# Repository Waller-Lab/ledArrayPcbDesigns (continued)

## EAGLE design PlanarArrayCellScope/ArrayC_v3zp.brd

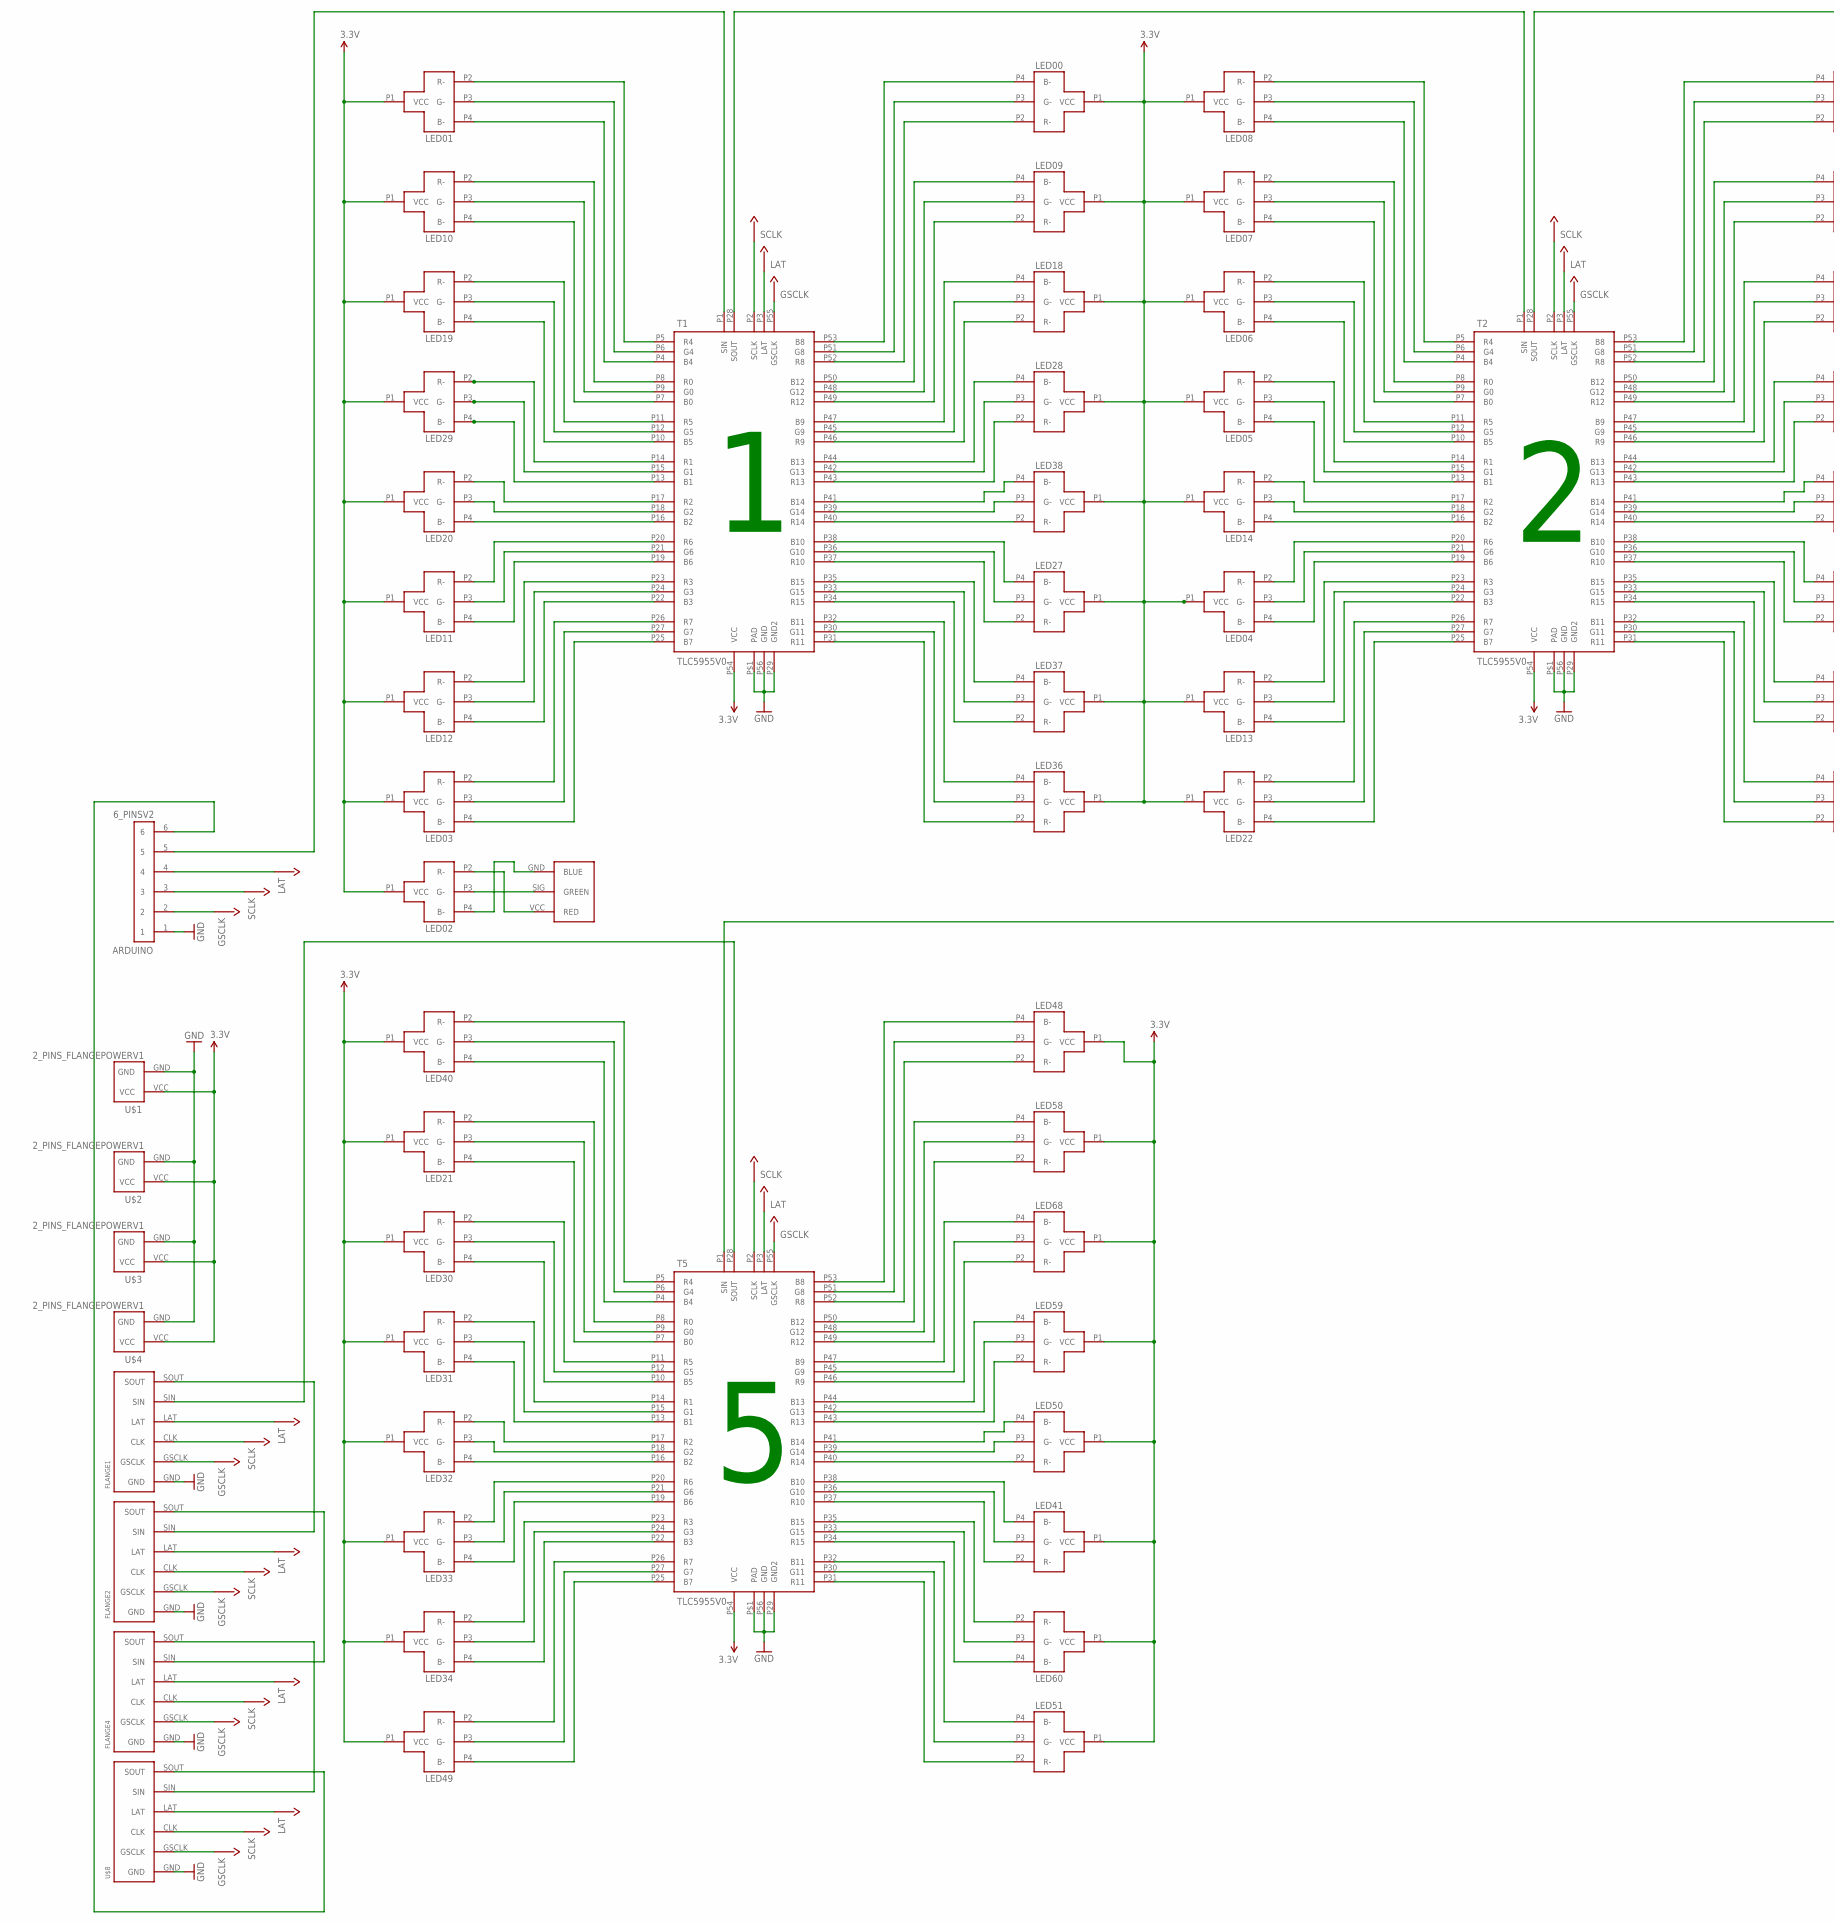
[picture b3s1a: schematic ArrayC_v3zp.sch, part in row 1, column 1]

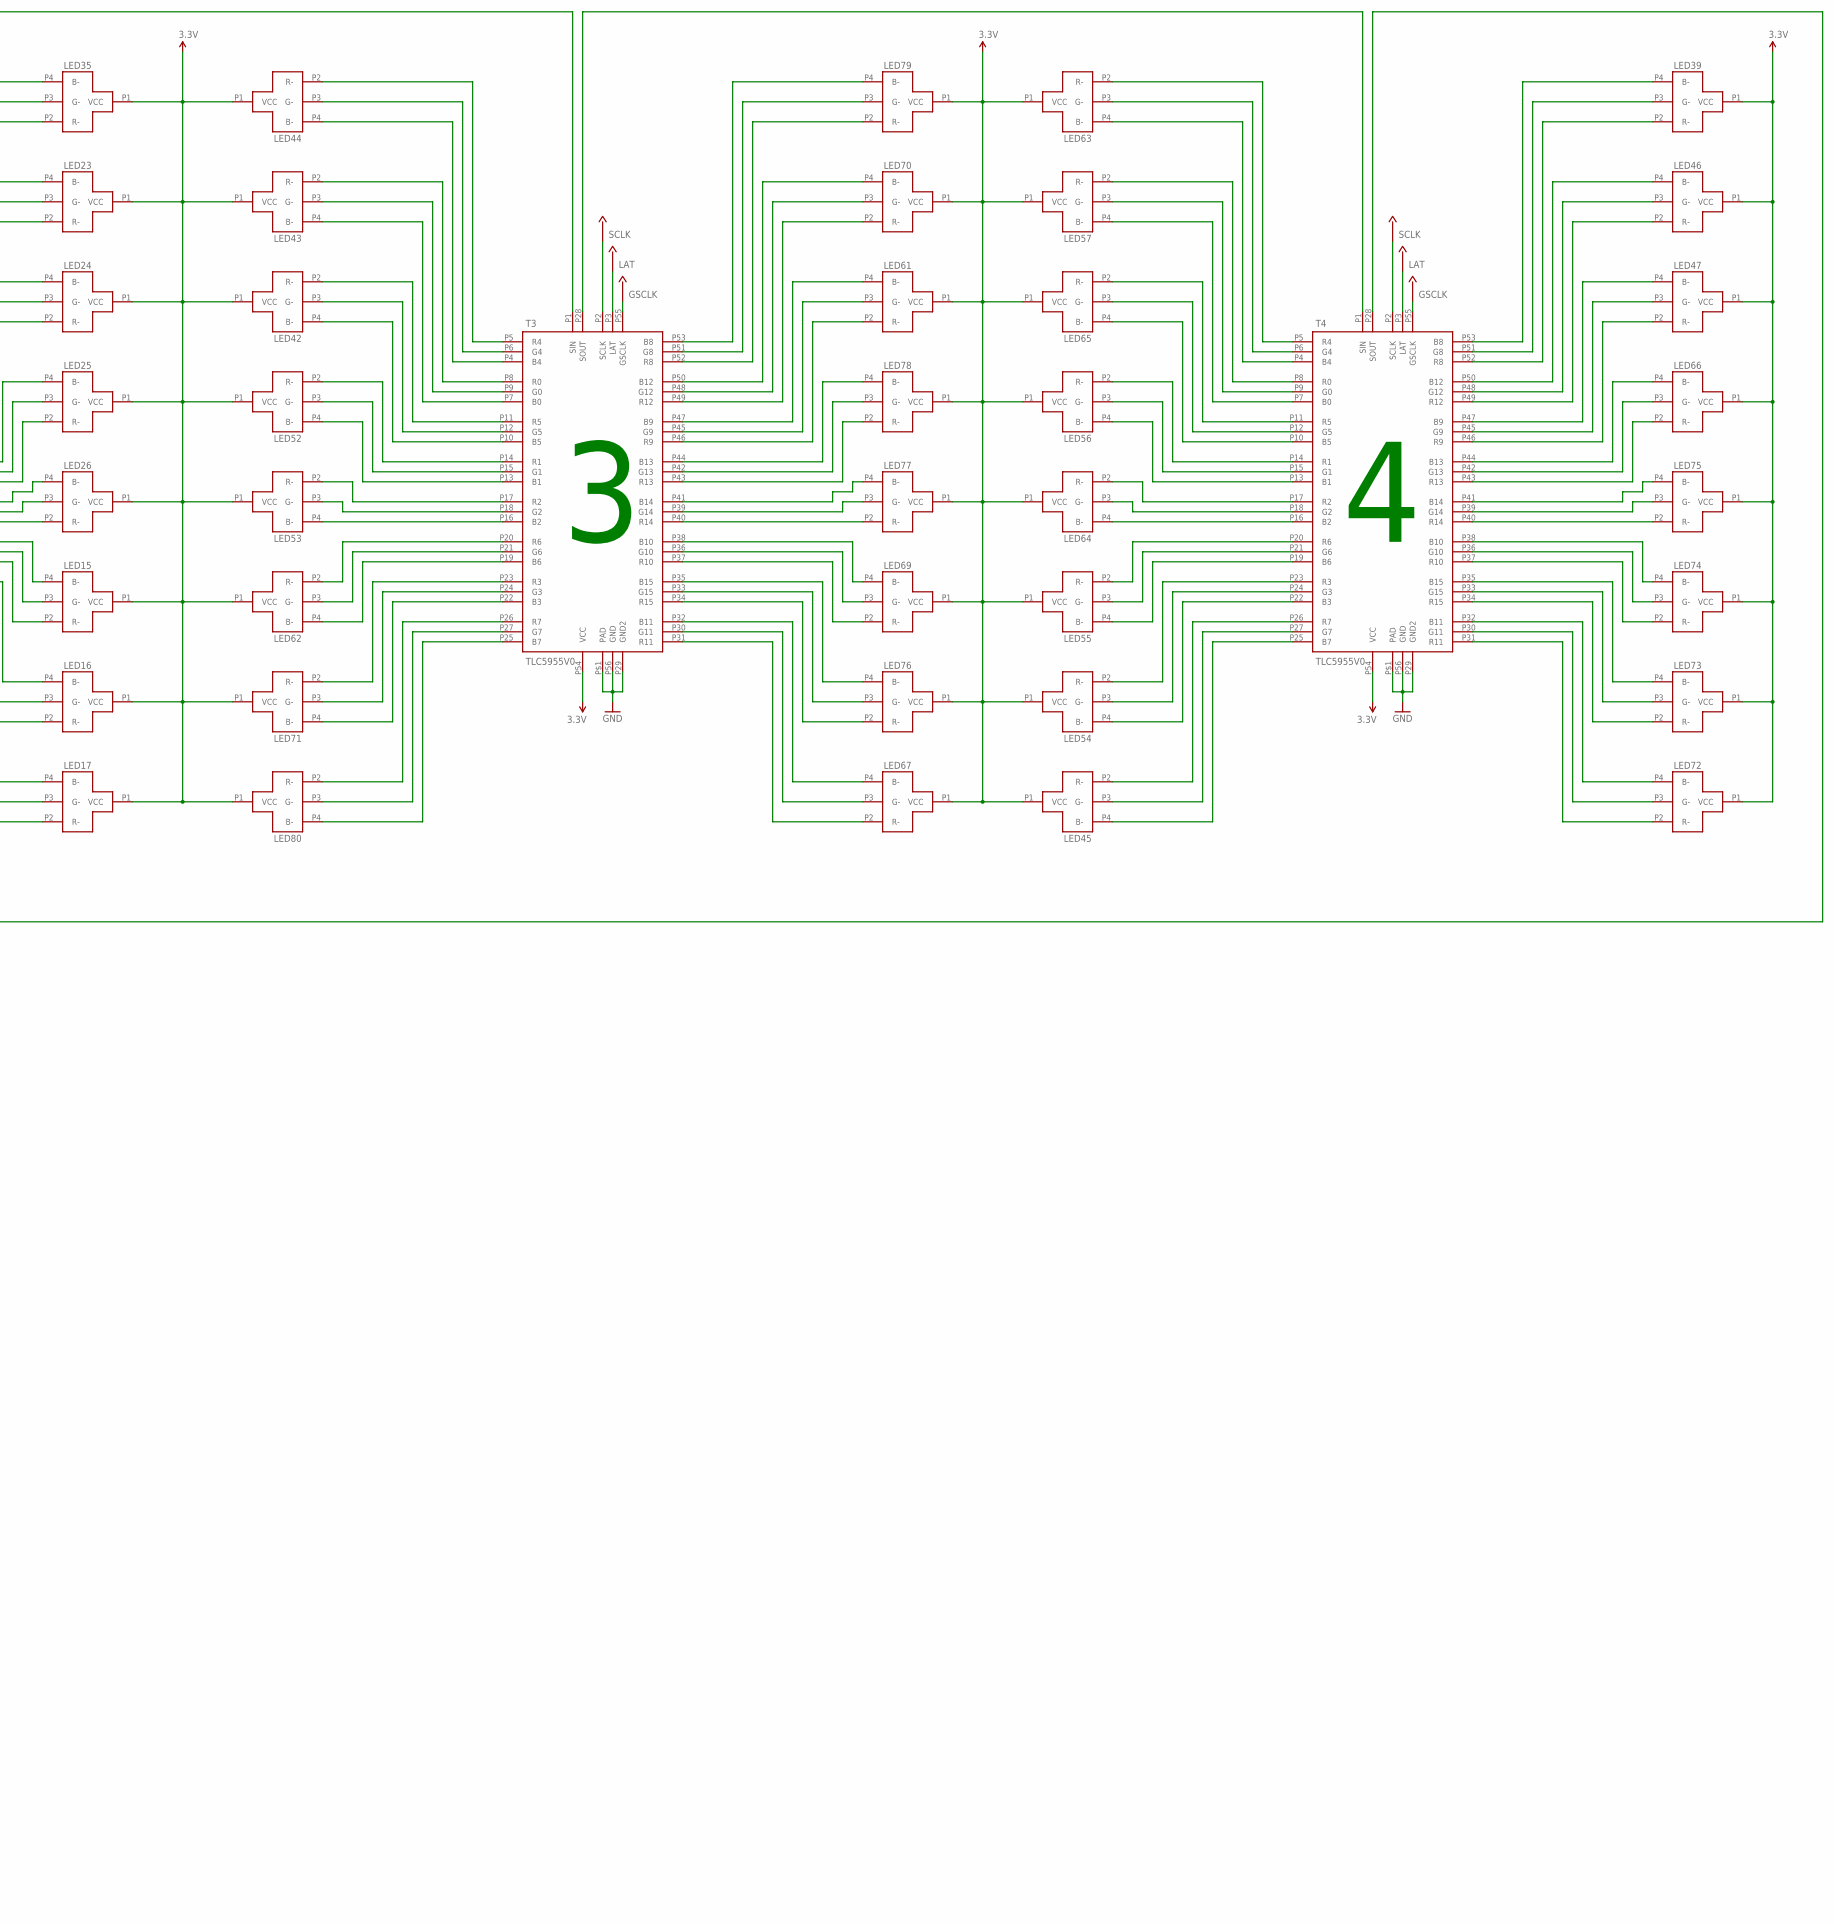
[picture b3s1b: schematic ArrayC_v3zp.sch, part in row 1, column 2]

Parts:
ARDUINO: 6_PINSV2; 6PIN_SMD
FLANGE1, FLANGE2, FLANGE4: 6PINS_LEDFLANGEV1; 6PIN_PADS
LED: 3_PINS_RGBV1; 3PIN_HOLES
LED00, LED01, LED02, LED03, LED04, LED05, LED06, LED07, LED08, LED09, LED10, LED11, LED12, LED13, LED14, LED15, LED16, LED17, LED18, LED19, LED20, LED21, LED22, LED23, LED24, LED25, LED26, LED27, LED28, LED29, LED30, LED31, LED32, LED33, LED34, LED35, LED36, LED37, LED38, LED39, LED40, LED41, LED42, LED43, LED44, LED45, LED46, LED47, LED48, LED49, LED50, LED51, LED52, LED53, LED54, LED55, LED56, LED57, LED58, LED59, LED60, LED61, LED62, LED63, LED64, LED65, LED66, LED67, LED68, LED69, LED70, LED71, LED72, LED73, LED74, LED75, LED76, LED77, LED78, LED79, LED80: KB_APTF1616V0; KB_RGBLED_APTF1616
T1, T2, T3, T4, T5: TLC5955V0; 56-HTSSOP
U$1, U$2, U$3, U$4: 2_PINS_FLANGEPOWERV1; 2PIN_PADS_PWR
U$8: 6PINS_LEDFLANGEV1; 6PIN_PADS

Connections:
3.3V: LED01.P1 (VCC), LED02.P1 (VCC), LED03.P1 (VCC), LED10.P1 (VCC), LED11.P1 (VCC), LED12.P1 (VCC), LED19.P1 (VCC), LED20.P1 (VCC), LED21.P1 (VCC), LED29.P1 (VCC), LED30.P1 (VCC), LED31.P1 (VCC), LED32.P1 (VCC), LED33.P1 (VCC), LED34.P1 (VCC), LED39.P1 (VCC), LED40.P1 (VCC), LED41.P1 (VCC), LED45.P1 (VCC), LED46.P1 (VCC), LED47.P1 (VCC), LED48.P1 (VCC), LED49.P1 (VCC), LED50.P1 (VCC), LED51.P1 (VCC), LED54.P1 (VCC), LED55.P1 (VCC), LED56.P1 (VCC), LED57.P1 (VCC), LED58.P1 (VCC), LED59.P1 (VCC), LED60.P1 (VCC), LED61.P1 (VCC), LED63.P1 (VCC), LED64.P1 (VCC), LED65.P1 (VCC), LED66.P1 (VCC), LED67.P1 (VCC), LED68.P1 (VCC), LED69.P1 (VCC), LED70.P1 (VCC), LED72.P1 (VCC), LED73.P1 (VCC), LED74.P1 (VCC), LED75.P1 (VCC), LED76.P1 (VCC), LED77.P1 (VCC), LED78.P1 (VCC), LED79.P1 (VCC), T1.P54 (VCC), T2.P54 (VCC), T3.P54 (VCC), T4.P54 (VCC), T5.P54 (VCC), U$1.VCC, U$2.VCC, U$3.VCC, U$4.VCC
GND: ARDUINO.1, FLANGE1.GND, FLANGE2.GND, FLANGE4.GND, T1.P29 (GND2), T1.P56 (GND), T1.P$1 (PAD), T2.P29 (GND2), T2.P56 (GND), T2.P$1 (PAD), T3.P29 (GND2), T3.P56 (GND), T3.P$1 (PAD), T4.P29 (GND2), T4.P56 (GND), T4.P$1 (PAD), T5.P29 (GND2), T5.P56 (GND), T5.P$1 (PAD), U$1.GND, U$2.GND, U$3.GND, U$4.GND, U$8.GND
GSCLK: ARDUINO.2, FLANGE1.GSCLK, FLANGE2.GSCLK, FLANGE4.GSCLK, T1.P55 (GSCLK), T2.P55 (GSCLK), T3.P55 (GSCLK), T4.P55 (GSCLK), T5.P55 (GSCLK), U$8.GSCLK
LAT: ARDUINO.4, FLANGE1.LAT, FLANGE2.LAT, FLANGE4.LAT, T1.P3 (LAT), T2.P3 (LAT), T3.P3 (LAT), T4.P3 (LAT), T5.P3 (LAT), U$8.LAT
unnamed: LED40.P2 (R-), T5.P5 (R4)
unnamed: LED40.P3 (G-), T5.P6 (G4)
unnamed: LED40.P4 (B-), T5.P4 (B4)
unnamed: LED21.P2 (R-), T5.P8 (R0)
unnamed: LED21.P3 (G-), T5.P9 (G0)
unnamed: LED21.P4 (B-), T5.P7 (B0)
unnamed: LED30.P2 (R-), T5.P11 (R5)
unnamed: LED30.P3 (G-), T5.P12 (G5)
unnamed: LED30.P4 (B-), T5.P10 (B5)
unnamed: LED31.P2 (R-), T5.P14 (R1)
unnamed: LED31.P3 (G-), T5.P15 (G1)
unnamed: LED31.P4 (B-), T5.P13 (B1)
unnamed: LED32.P2 (R-), T5.P17 (R2)
unnamed: LED32.P3 (G-), T5.P18 (G2)
unnamed: LED32.P4 (B-), T5.P16 (B2)
unnamed: LED33.P2 (R-), T5.P20 (R6)
unnamed: LED33.P3 (G-), T5.P21 (G6)
unnamed: LED33.P4 (B-), T5.P19 (B6)
unnamed: LED34.P2 (R-), T5.P23 (R3)
unnamed: LED34.P3 (G-), T5.P24 (G3)
unnamed: LED34.P4 (B-), T5.P22 (B3)
unnamed: LED49.P2 (R-), T5.P26 (R7)
unnamed: LED49.P3 (G-), T5.P27 (G7)
unnamed: LED49.P4 (B-), T5.P25 (B7)
unnamed: LED48.P4 (B-), T5.P53 (B8)
unnamed: LED48.P3 (G-), T5.P51 (G8)
unnamed: LED48.P2 (R-), T5.P52 (R8)
unnamed: LED58.P4 (B-), T5.P50 (B12)
unnamed: LED58.P3 (G-), T5.P48 (G12)
unnamed: LED58.P2 (R-), T5.P49 (R12)
unnamed: LED68.P4 (B-), T5.P47 (B9)
unnamed: LED68.P3 (G-), T5.P45 (G9)
unnamed: LED68.P2 (R-), T5.P46 (R9)
unnamed: LED59.P4 (B-), T5.P44 (B13)
unnamed: LED59.P3 (G-), T5.P42 (G13)
unnamed: LED50.P4 (B-), T5.P41 (B14)
unnamed: LED50.P3 (G-), T5.P39 (G14)
unnamed: LED50.P2 (R-), T5.P40 (R14)
unnamed: LED41.P4 (B-), T5.P38 (B10)
unnamed: LED41.P3 (G-), T5.P36 (G10)
unnamed: LED41.P2 (R-), T5.P37 (R10)
unnamed: LED60.P2 (R-), T5.P35 (B15)
unnamed: LED60.P3 (G-), T5.P33 (G15)
unnamed: LED60.P4 (B-), T5.P34 (R15)
unnamed: LED51.P4 (B-), T5.P32 (B11)
unnamed: LED51.P3 (G-), T5.P30 (G11)
unnamed: LED51.P2 (R-), T5.P31 (R11)
unnamed: LED.VCC (RED), LED02.P2 (R-)
unnamed: LED.GND (BLUE), LED02.P4 (B-)
unnamed: LED.SIG (GREEN), LED02.P3 (G-)
unnamed: FLANGE1.SOUT, FLANGE2.SIN
unnamed: FLANGE2.SOUT, FLANGE4.SIN
unnamed: ARDUINO.6, U$8.SOUT
unnamed: FLANGE4.SOUT, U$8.SIN
unnamed: LED01.P2 (R-), T1.P5 (R4)
unnamed: LED01.P3 (G-), T1.P6 (G4)
unnamed: LED01.P4 (B-), T1.P4 (B4)
unnamed: LED10.P2 (R-), T1.P8 (R0)
unnamed: LED10.P3 (G-), T1.P9 (G0)
unnamed: LED10.P4 (B-), T1.P7 (B0)
unnamed: LED19.P2 (R-), T1.P11 (R5)
unnamed: LED19.P3 (G-), T1.P12 (G5)
unnamed: LED19.P4 (B-), T1.P10 (B5)
unnamed: LED29.P2 (R-), T1.P14 (R1)
unnamed: LED29.P3 (G-), T1.P15 (G1)
unnamed: LED29.P4 (B-), T1.P13 (B1)
unnamed: LED20.P2 (R-), T1.P17 (R2)
unnamed: LED20.P3 (G-), T1.P18 (G2)
unnamed: LED20.P4 (B-), T1.P16 (B2)
unnamed: LED11.P2 (R-), T1.P20 (R6)
unnamed: LED11.P3 (G-), T1.P21 (G6)
unnamed: LED11.P4 (B-), T1.P19 (B6)
unnamed: LED12.P2 (R-), T1.P23 (R3)
unnamed: LED12.P3 (G-), T1.P24 (G3)
unnamed: LED12.P4 (B-), T1.P22 (B3)
unnamed: LED03.P2 (R-), T1.P26 (R7)
unnamed: LED03.P3 (G-), T1.P27 (G7)
unnamed: LED03.P4 (B-), T1.P25 (B7)
unnamed: LED00.P4 (B-), T1.P53 (B8)
unnamed: LED00.P3 (G-), T1.P51 (G8)
unnamed: LED00.P2 (R-), T1.P52 (R8)
unnamed: LED09.P4 (B-), T1.P50 (B12)
unnamed: LED09.P3 (G-), T1.P48 (G12)
unnamed: LED09.P2 (R-), T1.P49 (R12)
unnamed: LED18.P4 (B-), T1.P47 (B9)
unnamed: LED18.P3 (G-), T1.P45 (G9)
unnamed: LED18.P2 (R-), T1.P46 (R9)
unnamed: LED28.P4 (B-), T1.P44 (B13)
unnamed: LED28.P3 (G-), T1.P42 (G13)
unnamed: LED38.P4 (B-), T1.P41 (B14)
unnamed: LED38.P3 (G-), T1.P39 (G14)
unnamed: LED38.P2 (R-), T1.P40 (R14)
unnamed: LED27.P4 (B-), T1.P38 (B10)
unnamed: LED27.P3 (G-), T1.P36 (G10)
unnamed: LED27.P2 (R-), T1.P37 (R10)
unnamed: LED37.P4 (B-), T1.P35 (B15)
unnamed: LED37.P3 (G-), T1.P33 (G15)
unnamed: LED37.P2 (R-), T1.P34 (R15)
unnamed: LED36.P4 (B-), T1.P32 (B11)
unnamed: LED36.P3 (G-), T1.P30 (G11)
unnamed: LED36.P2 (R-), T1.P31 (R11)
unnamed: LED44.P2 (R-), T3.P5 (R4)
unnamed: LED08.P2 (R-), T2.P5 (R4)
unnamed: LED08.P3 (G-), T2.P6 (G4)
unnamed: LED08.P4 (B-), T2.P4 (B4)
unnamed: LED07.P2 (R-), T2.P8 (R0)
unnamed: LED07.P3 (G-), T2.P9 (G0)
unnamed: LED07.P4 (B-), T2.P7 (B0)
unnamed: LED06.P2 (R-), T2.P11 (R5)
unnamed: LED06.P3 (G-), T2.P12 (G5)
unnamed: LED06.P4 (B-), T2.P10 (B5)
unnamed: LED05.P2 (R-), T2.P14 (R1)
unnamed: LED05.P3 (G-), T2.P15 (G1)
unnamed: LED05.P4 (B-), T2.P13 (B1)
unnamed: LED14.P2 (R-), T2.P17 (R2)
unnamed: LED14.P3 (G-), T2.P18 (G2)
unnamed: LED14.P4 (B-), T2.P16 (B2)
unnamed: LED04.P2 (R-), T2.P20 (R6)
unnamed: LED04.P3 (G-), T2.P21 (G6)
unnamed: LED04.P4 (B-), T2.P19 (B6)
unnamed: LED13.P2 (R-), T2.P23 (R3)
unnamed: LED13.P3 (G-), T2.P24 (G3)
unnamed: LED13.P4 (B-), T2.P22 (B3)
unnamed: LED22.P2 (R-), T2.P26 (R7)
unnamed: LED22.P3 (G-), T2.P27 (G7)
unnamed: LED22.P4 (B-), T2.P25 (B7)
unnamed: LED35.P4 (B-), T2.P53 (B8)
unnamed: LED35.P3 (G-), T2.P51 (G8)
unnamed: LED35.P2 (R-), T2.P52 (R8)
unnamed: LED23.P4 (B-), T2.P50 (B12)
unnamed: LED23.P3 (G-), T2.P48 (G12)
unnamed: LED23.P2 (R-), T2.P49 (R12)
unnamed: LED24.P4 (B-), T2.P47 (B9)
unnamed: LED24.P3 (G-), T2.P45 (G9)
unnamed: LED24.P2 (R-), T2.P46 (R9)
unnamed: LED25.P4 (B-), T2.P44 (B13)
unnamed: LED25.P3 (G-), T2.P42 (G13)
unnamed: LED26.P4 (B-), T2.P41 (B14)
unnamed: LED26.P3 (G-), T2.P39 (G14)
unnamed: LED26.P2 (R-), T2.P40 (R14)
unnamed: LED15.P4 (B-), T2.P38 (B10)
unnamed: LED15.P3 (G-), T2.P36 (G10)
unnamed: LED15.P2 (R-), T2.P37 (R10)
unnamed: LED16.P4 (B-), T2.P35 (B15)
unnamed: LED16.P3 (G-), T2.P33 (G15)
unnamed: LED16.P2 (R-), T2.P34 (R15)
unnamed: LED17.P4 (B-), T2.P32 (B11)
unnamed: LED17.P3 (G-), T2.P30 (G11)
unnamed: LED17.P2 (R-), T2.P31 (R11)
unnamed: LED44.P3 (G-), T3.P6 (G4)
unnamed: LED44.P4 (B-), T3.P4 (B4)
unnamed: LED43.P2 (R-), T3.P8 (R0)
unnamed: LED43.P3 (G-), T3.P9 (G0)
unnamed: LED43.P4 (B-), T3.P7 (B0)
unnamed: LED42.P2 (R-), T3.P11 (R5)
unnamed: LED42.P3 (G-), T3.P12 (G5)
unnamed: LED42.P4 (B-), T3.P10 (B5)
unnamed: LED52.P2 (R-), T3.P14 (R1)
unnamed: LED52.P3 (G-), T3.P15 (G1)
unnamed: LED52.P4 (B-), T3.P13 (B1)
unnamed: LED53.P2 (R-), T3.P17 (R2)
unnamed: LED53.P3 (G-), T3.P18 (G2)
unnamed: LED53.P4 (B-), T3.P16 (B2)
unnamed: LED62.P2 (R-), T3.P20 (R6)
unnamed: LED62.P3 (G-), T3.P21 (G6)
unnamed: LED62.P4 (B-), T3.P19 (B6)
unnamed: LED71.P2 (R-), T3.P23 (R3)
unnamed: LED71.P3 (G-), T3.P24 (G3)
unnamed: LED71.P4 (B-), T3.P22 (B3)
unnamed: LED80.P2 (R-), T3.P26 (R7)
unnamed: LED80.P3 (G-), T3.P27 (G7)
unnamed: LED80.P4 (B-), T3.P25 (B7)
unnamed: LED79.P4 (B-), T3.P53 (B8)
unnamed: LED79.P3 (G-), T3.P51 (G8)
unnamed: LED79.P2 (R-), T3.P52 (R8)
unnamed: LED70.P4 (B-), T3.P50 (B12)
unnamed: LED70.P3 (G-), T3.P48 (G12)
unnamed: LED70.P2 (R-), T3.P49 (R12)
unnamed: LED61.P4 (B-), T3.P47 (B9)
unnamed: LED61.P3 (G-), T3.P45 (G9)
unnamed: LED61.P2 (R-), T3.P46 (R9)
unnamed: LED78.P4 (B-), T3.P44 (B13)
unnamed: LED78.P3 (G-), T3.P42 (G13)
unnamed: LED77.P4 (B-), T3.P41 (B14)
unnamed: LED77.P3 (G-), T3.P39 (G14)
unnamed: LED77.P2 (R-), T3.P40 (R14)
unnamed: LED69.P4 (B-), T3.P38 (B10)
unnamed: LED69.P3 (G-), T3.P36 (G10)
unnamed: LED69.P2 (R-), T3.P37 (R10)
unnamed: LED76.P4 (B-), T3.P35 (B15)
unnamed: LED76.P3 (G-), T3.P33 (G15)
unnamed: LED76.P2 (R-), T3.P34 (R15)
unnamed: LED67.P4 (B-), T3.P32 (B11)
unnamed: LED67.P3 (G-), T3.P30 (G11)
unnamed: LED67.P2 (R-), T3.P31 (R11)
unnamed: LED63.P2 (R-), T4.P5 (R4)
unnamed: LED63.P3 (G-), T4.P6 (G4)
unnamed: LED63.P4 (B-), T4.P4 (B4)
unnamed: LED57.P2 (R-), T4.P8 (R0)
unnamed: LED57.P3 (G-), T4.P9 (G0)
unnamed: LED57.P4 (B-), T4.P7 (B0)
unnamed: LED65.P2 (R-), T4.P11 (R5)
unnamed: LED65.P3 (G-), T4.P12 (G5)
unnamed: LED65.P4 (B-), T4.P10 (B5)
unnamed: LED56.P2 (R-), T4.P14 (R1)
unnamed: LED56.P3 (G-), T4.P15 (G1)
unnamed: LED56.P4 (B-), T4.P13 (B1)
unnamed: LED64.P2 (R-), T4.P17 (R2)
unnamed: LED64.P3 (G-), T4.P18 (G2)
unnamed: LED64.P4 (B-), T4.P16 (B2)
unnamed: LED55.P2 (R-), T4.P20 (R6)
unnamed: LED55.P3 (G-), T4.P21 (G6)
unnamed: LED55.P4 (B-), T4.P19 (B6)
unnamed: LED54.P2 (R-), T4.P23 (R3)
unnamed: LED54.P3 (G-), T4.P24 (G3)
unnamed: LED54.P4 (B-), T4.P22 (B3)
unnamed: LED45.P2 (R-), T4.P26 (R7)
unnamed: LED45.P3 (G-), T4.P27 (G7)
unnamed: LED45.P4 (B-), T4.P25 (B7)
unnamed: LED39.P4 (B-), T4.P53 (B8)
unnamed: LED39.P3 (G-), T4.P51 (G8)
unnamed: LED39.P2 (R-), T4.P52 (R8)
unnamed: LED46.P4 (B-), T4.P50 (B12)
unnamed: LED46.P3 (G-), T4.P48 (G12)
unnamed: LED46.P2 (R-), T4.P49 (R12)
unnamed: LED47.P4 (B-), T4.P47 (B9)
unnamed: LED47.P3 (G-), T4.P45 (G9)
unnamed: LED47.P2 (R-), T4.P46 (R9)
unnamed: LED66.P4 (B-), T4.P44 (B13)
unnamed: LED66.P3 (G-), T4.P42 (G13)
unnamed: LED75.P4 (B-), T4.P41 (B14)
unnamed: LED75.P3 (G-), T4.P39 (G14)
unnamed: LED75.P2 (R-), T4.P40 (R14)
unnamed: LED74.P4 (B-), T4.P38 (B10)
unnamed: LED74.P3 (G-), T4.P36 (G10)
unnamed: LED74.P2 (R-), T4.P37 (R10)
unnamed: LED73.P4 (B-), T4.P35 (B15)
unnamed: LED73.P3 (G-), T4.P33 (G15)
unnamed: LED73.P2 (R-), T4.P34 (R15)
unnamed: LED72.P4 (B-), T4.P32 (B11)
unnamed: LED72.P3 (G-), T4.P30 (G11)
unnamed: LED72.P2 (R-), T4.P31 (R11)
unnamed: FLANGE1.SIN, T5.P28 (SOUT)
unnamed: T4.P28 (SOUT), T5.P1 (SIN)
unnamed: T3.P28 (SOUT), T4.P1 (SIN)
unnamed: T2.P28 (SOUT), T3.P1 (SIN)
unnamed: T1.P28 (SOUT), T2.P1 (SIN)
unnamed: LED66.P2 (R-), T4.P43 (R13)
unnamed: ARDUINO.5, T1.P1 (SIN)
unnamed: LED59.P2 (R-), T5.P43 (R13)
unnamed: LED78.P2 (R-), T3.P43 (R13)
unnamed: LED25.P2 (R-), T2.P43 (R13)
unnamed: LED00.P1 (VCC), LED04.P1 (VCC), LED05.P1 (VCC), LED06.P1 (VCC), LED07.P1 (VCC), LED08.P1 (VCC), LED09.P1 (VCC), LED13.P1 (VCC), LED14.P1 (VCC), LED18.P1 (VCC), LED22.P1 (VCC), LED27.P1 (VCC), LED28.P1 (VCC), LED36.P1 (VCC), LED37.P1 (VCC), LED38.P1 (VCC)
unnamed: LED28.P2 (R-), T1.P43 (R13)
unnamed: LED15.P1 (VCC), LED16.P1 (VCC), LED17.P1 (VCC), LED23.P1 (VCC), LED24.P1 (VCC), LED25.P1 (VCC), LED26.P1 (VCC), LED35.P1 (VCC), LED42.P1 (VCC), LED43.P1 (VCC), LED44.P1 (VCC), LED52.P1 (VCC), LED53.P1 (VCC), LED62.P1 (VCC), LED71.P1 (VCC), LED80.P1 (VCC)
SCLK: ARDUINO.3, FLANGE1.CLK, FLANGE2.CLK, FLANGE4.CLK, T1.P2 (SCLK), T2.P2 (SCLK), T3.P2 (SCLK), T4.P2 (SCLK), T5.P2 (SCLK), U$8.CLK

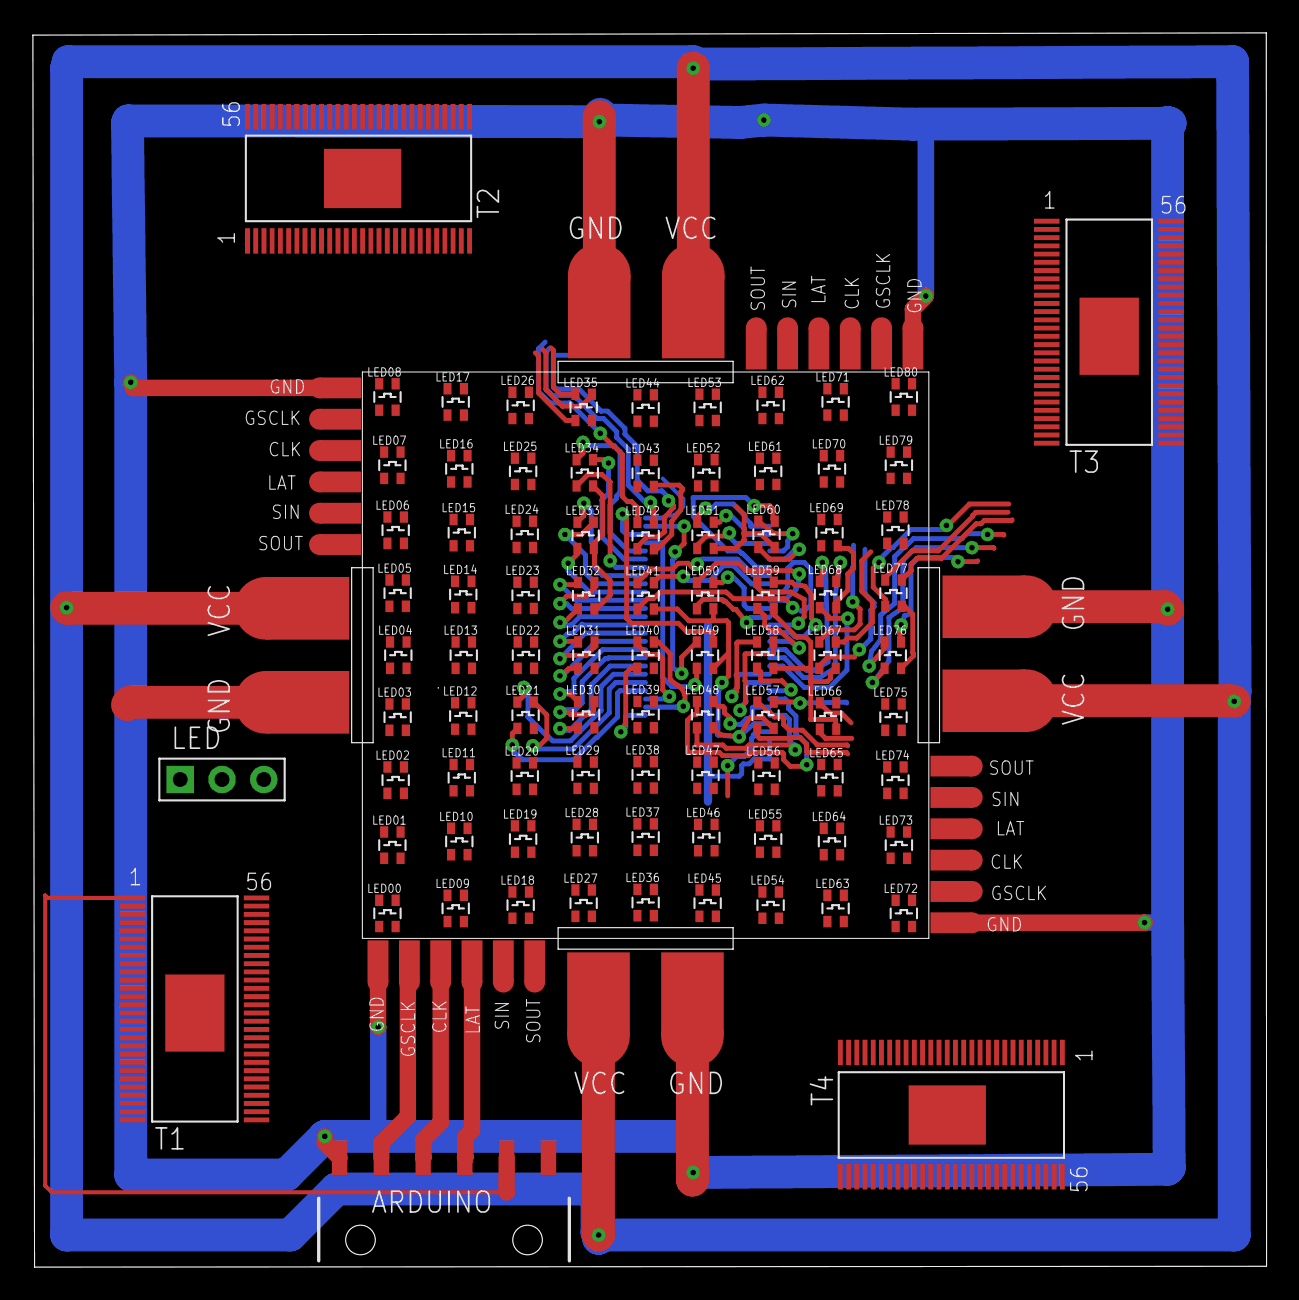
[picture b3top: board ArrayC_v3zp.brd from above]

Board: 2 copper layers, 75.0 x 75.0 mm, 96 parts (1 on the bottom side), 260 nets.

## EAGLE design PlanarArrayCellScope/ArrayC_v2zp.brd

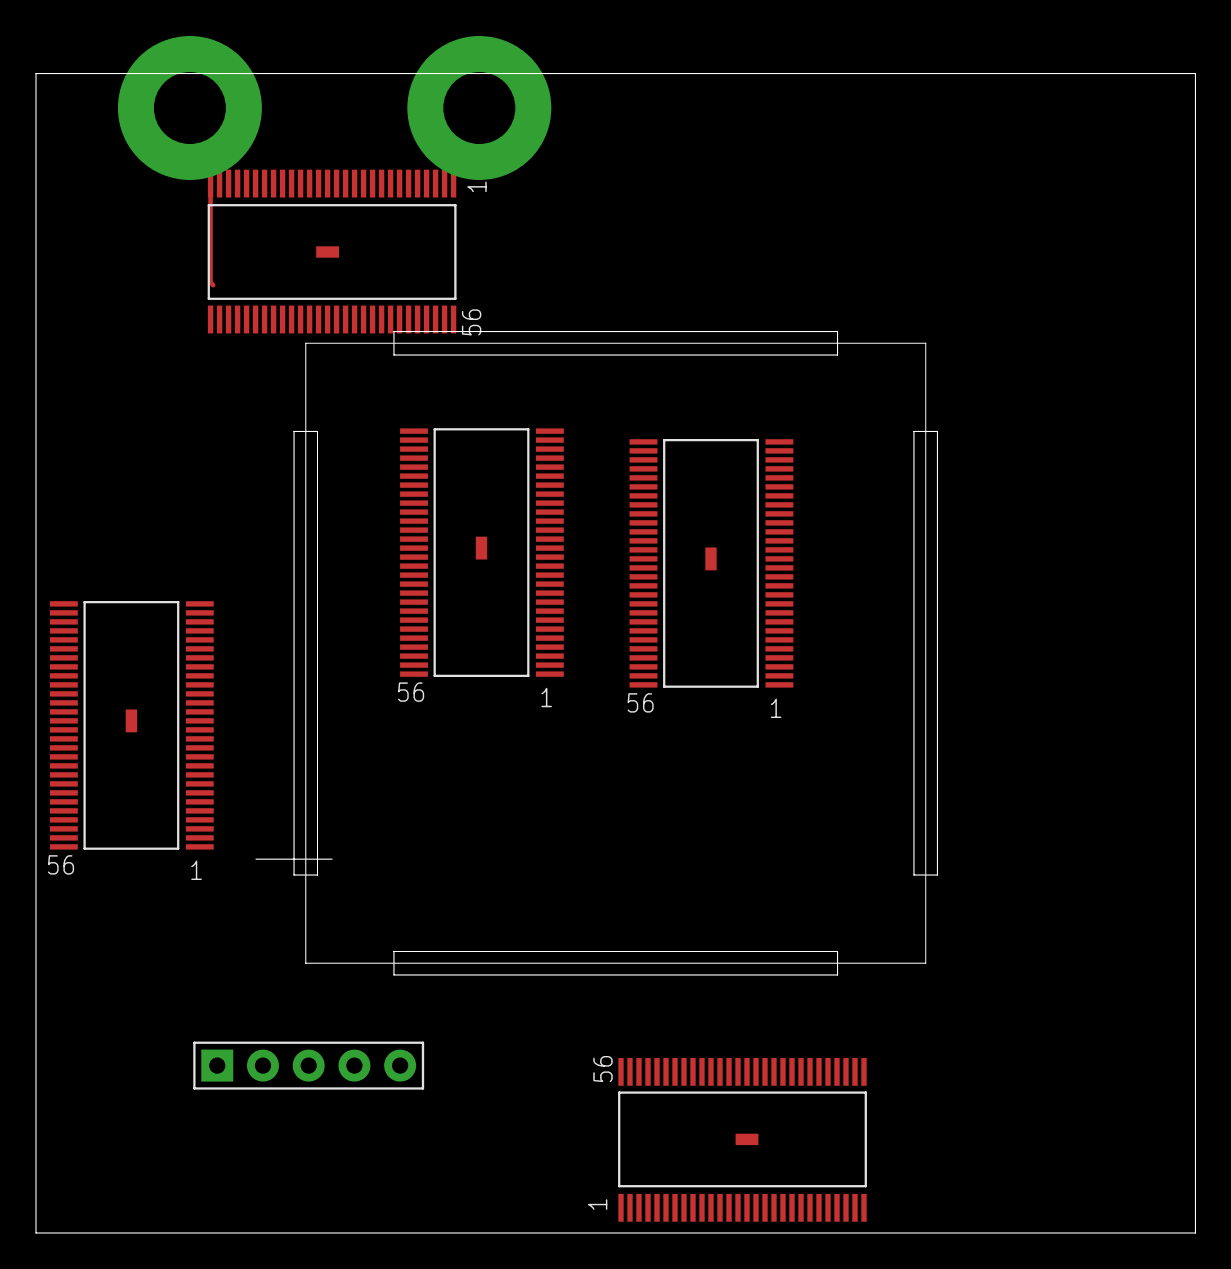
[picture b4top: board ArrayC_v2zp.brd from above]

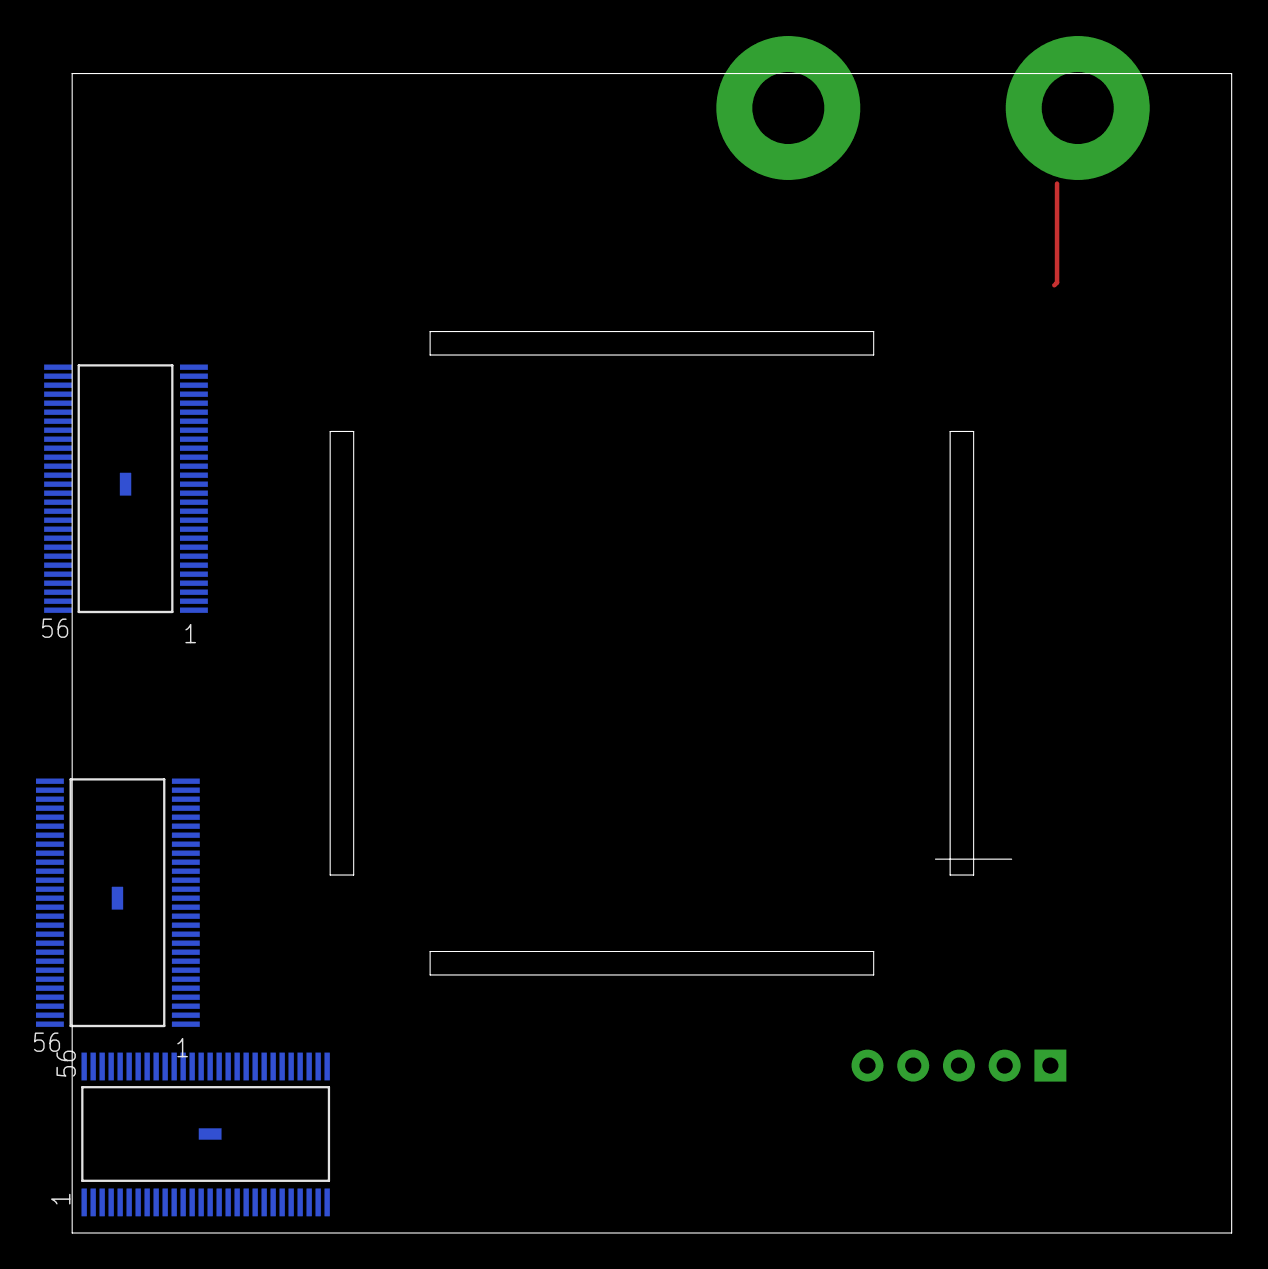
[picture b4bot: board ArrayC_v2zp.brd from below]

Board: 2 copper layers, 64.4 x 64.4 mm, 10 parts (3 on the bottom side), 14 nets.

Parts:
U$1, U$2, U$3, U$4, U$5, U$6, U$7, U$8: TLC5955V0; 56-HTSSOP
U$9: 5_PINSV1; 5PIN_HOLES
U$10: 2PIN_PWR0.1HEADER; 2PIN_HOLES_PWR

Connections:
3.3V: U$1.P54, U$2.P54, U$3.P54, U$4.P54, U$5.P54, U$6.P54, U$7.P54, U$8.P54, U$10.P$2
GND: U$1.P29, U$1.P56, U$1.P$1, U$2.P29, U$2.P56, U$2.P$1, U$3.P29, U$3.P56, U$3.P$1, U$4.P29, U$4.P56, U$4.P$1, U$5.P29, U$5.P56, U$5.P$1, U$6.P29, U$6.P56, U$6.P$1, U$7.P29, U$7.P56, U$7.P$1, U$8.P29, U$8.P56, U$8.P$1, U$10.P$1
GSCLK: U$1.P55, U$2.P55, U$3.P55, U$4.P55, U$5.P55, U$6.P55, U$7.P55, U$8.P55, U$9.P1
LAT: U$1.P3, U$2.P3, U$3.P3, U$4.P3, U$5.P3, U$6.P3, U$7.P3, U$8.P3, U$9.P2
unnamed: U$1.P28, U$2.P1
unnamed: U$2.P28, U$6.P1
unnamed: U$6.P28, U$8.P1
unnamed: U$1.P1, U$7.P28
unnamed: U$5.P28, U$7.P1
unnamed: U$4.P28, U$5.P1
unnamed: U$3.P28, U$4.P1
unnamed: U$3.P1, U$9.P5
unnamed: U$8.P28, U$9.P4
SCLK: U$1.P2, U$2.P2, U$3.P2, U$4.P2, U$5.P2, U$6.P2, U$7.P2, U$8.P2, U$9.P3

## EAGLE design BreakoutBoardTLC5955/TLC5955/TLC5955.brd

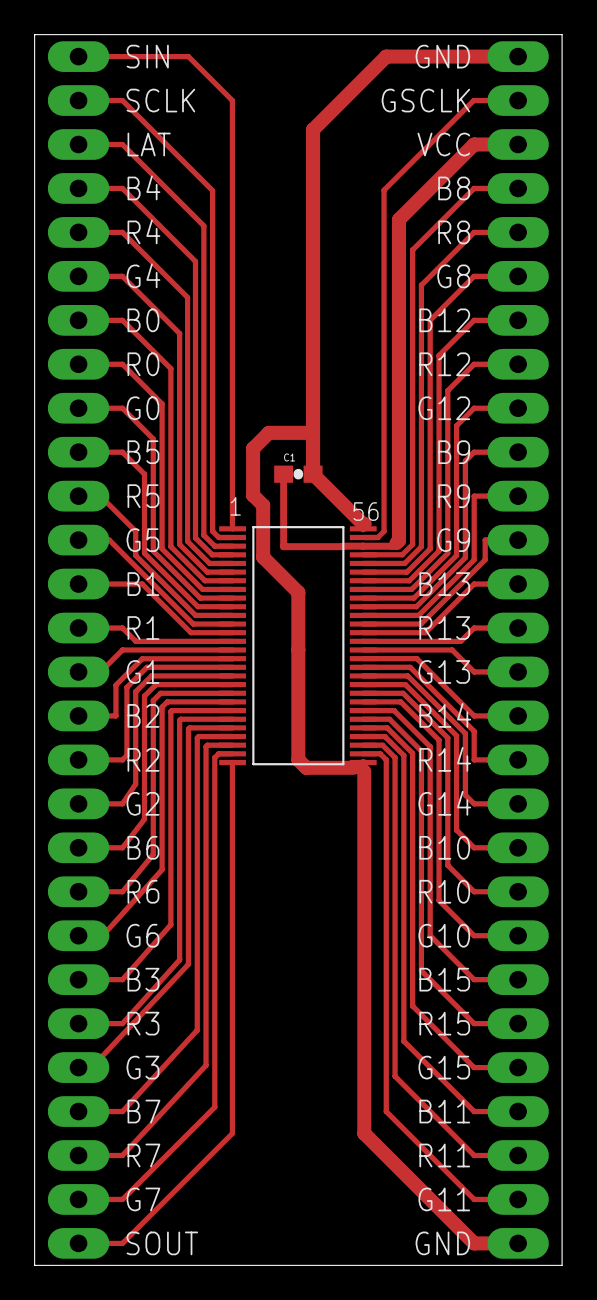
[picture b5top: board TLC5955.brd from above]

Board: 2 copper layers, 30.5 x 71.1 mm, 4 parts (0 on the bottom side), 55 nets.

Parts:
C1: 10uF; 0603-CAP
U$1: TLC5955V0; 56-HTSSOP
U$2, U$3: 28_PINS0; 28PIN_HOLES

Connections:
unnamed: U$1.P4, U$2.P4
unnamed: U$1.P5, U$2.P5
unnamed: U$1.P6, U$2.P6
unnamed: U$1.P7, U$2.P7
unnamed: U$1.P8, U$2.P8
unnamed: U$1.P21, U$2.P21
unnamed: U$1.P10, U$2.P10
unnamed: U$1.P11, U$2.P11
unnamed: U$1.P12, U$2.P12
unnamed: U$1.P13, U$2.P13
unnamed: U$1.P14, U$2.P14
unnamed: U$1.P15, U$2.P15
unnamed: U$1.P16, U$2.P16
unnamed: U$1.P17, U$2.P17
unnamed: U$1.P18, U$2.P18
unnamed: U$1.P19, U$2.P19
unnamed: U$1.P20, U$2.P20
unnamed: U$1.P22, U$2.P22
unnamed: U$1.P23, U$2.P23
unnamed: U$1.P24, U$2.P24
unnamed: U$1.P9, U$2.P9
unnamed: U$1.P25, U$2.P25
unnamed: U$1.P26, U$2.P26
unnamed: U$1.P28, U$2.P28
unnamed: U$1.P27, U$2.P27
unnamed: U$1.P1, U$2.P1
unnamed: U$1.P2, U$2.P2
unnamed: U$1.P3, U$2.P3
unnamed: U$1.P47, U$3.P19
unnamed: C1.1, U$1.P54, U$3.P26
unnamed: U$1.P30, U$3.P2
unnamed: U$1.P31, U$3.P3
unnamed: U$1.P32, U$3.P4
unnamed: U$1.P33, U$3.P5
unnamed: U$1.P34, U$3.P6
unnamed: U$1.P35, U$3.P7
unnamed: U$1.P36, U$3.P8
unnamed: U$1.P37, U$3.P9
unnamed: U$1.P38, U$3.P10
unnamed: U$1.P39, U$3.P11
unnamed: U$1.P40, U$3.P12
unnamed: U$1.P41, U$3.P13
unnamed: U$1.P42, U$3.P14
unnamed: U$1.P43, U$3.P15
unnamed: U$1.P44, U$3.P16
unnamed: U$1.P45, U$3.P17
unnamed: U$1.P46, U$3.P18
unnamed: U$1.P48, U$3.P20
unnamed: U$1.P49, U$3.P21
unnamed: U$1.P50, U$3.P22
unnamed: U$1.P51, U$3.P23
unnamed: U$1.P52, U$3.P24
unnamed: U$1.P53, U$3.P25
unnamed: U$1.P55, U$3.P27
unnamed: C1.2, U$1.P29, U$1.P56, U$1.P$1, U$3.P1, U$3.P28
